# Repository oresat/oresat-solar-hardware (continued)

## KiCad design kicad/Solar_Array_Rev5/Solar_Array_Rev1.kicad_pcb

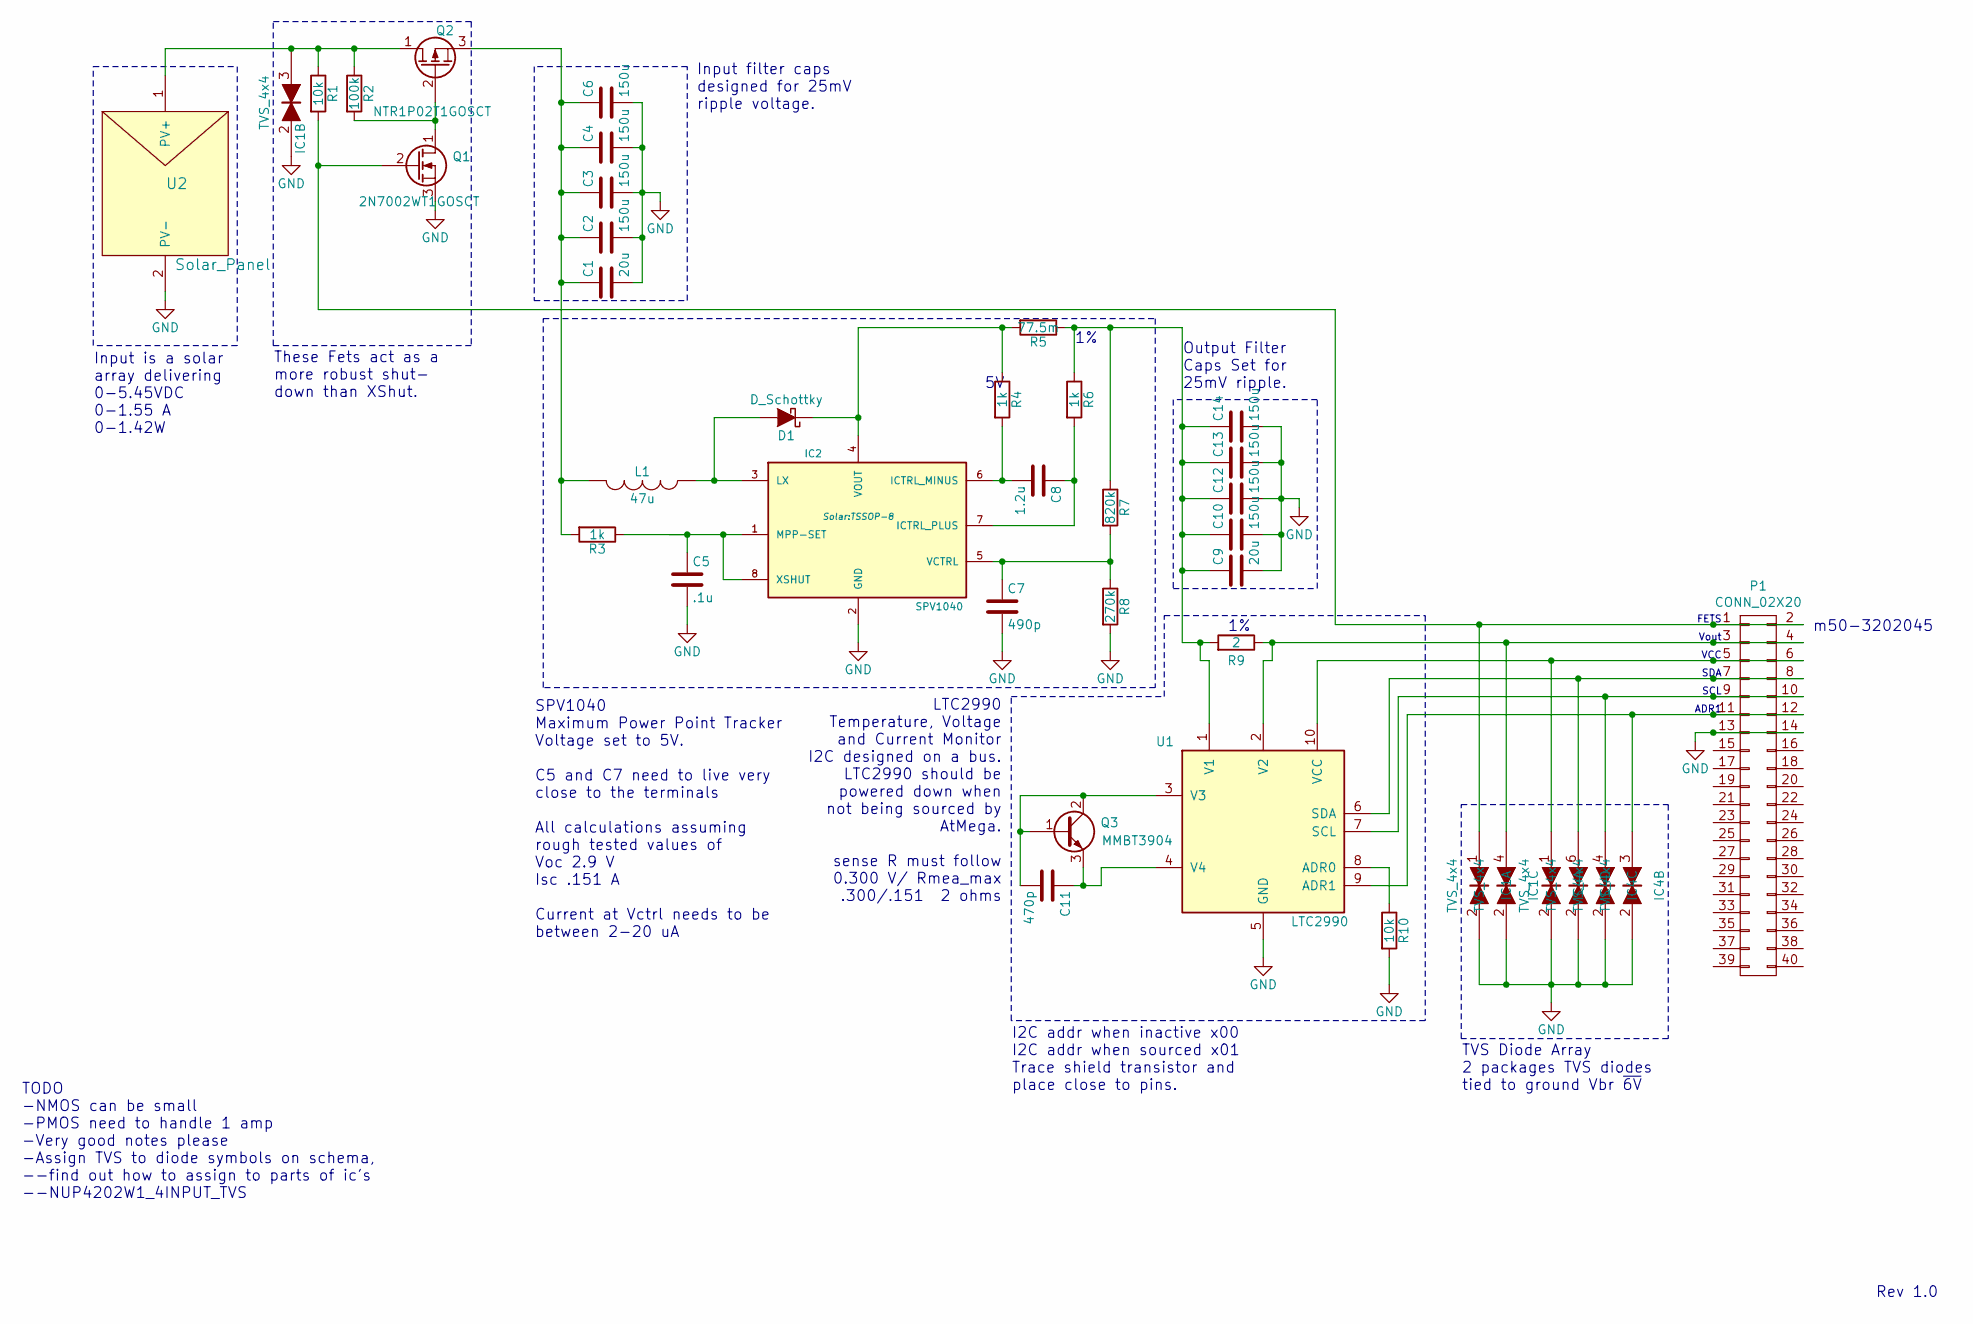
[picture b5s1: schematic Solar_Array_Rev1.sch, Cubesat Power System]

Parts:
C1, C9: 20u; C_0805
C2, C3, C4, C6, C10, C12, C13, C14: 150u; C_1210
C5: .1u; C_0603
C7: 490p; C_0603
C8: 1.2u; C_0805
C11: 470p; C_0805
D1: D_Schottky; SOD-323
IC1, IC4: TVS_4x4; SC-70-6
IC2: SPV1040; TSSOP-8
L1: 47u; Inductor_1212
P1: CONN_02X20; CS0_40PIN_HEADER
Q1: 2N7002WT1GOSCT; SC-70
Q2: NTR1P02T1GOSCT; SOT-23
Q3: MMBT3904; SOT-23
R1, R10: 10k; R_0603
R2: 100k; R_0603
R3, R4, R6: 1k; R_0603
R5: 77.5m; R_0603
R7: 820k; R_0603
R8: 270k; R_0603
R9: 2; R_0603
U1: LTC2990; MSOP-10
U2: Solar_Panel; ALTA_GA_CELL

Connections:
GND: C1.2, C2.2, C3.2, C4.2, C5.2, C6.2, C7.2, C9.2, C10.2, C12.2, C13.2, C14.2, IC1.2, IC2.2 (GND), IC4.2, P1.13, P1.14, Q1.3 (S), R8.2, R10.2, U1.5 (GND), U2.2 (PV-)
unnamed: C1.1, C2.1, C3.1, C4.1, C6.1, L1.2, Q2.3 (S), R3.2
unnamed: C5.1, IC2.1 (MPP-SET), IC2.8 (XSHUT), R3.1
unnamed: C7.1, IC2.5 (VCTRL), R7.2, R8.1
unnamed: C8.1, IC2.7 (ICTRL_PLUS), R6.2
unnamed: C8.2, IC2.6 (ICTRL_MINUS), R4.2
unnamed: C9.1, C10.1, C12.1, C13.1, C14.1, R5.1, R6.1, R7.1, R9.2, U1.1 (V1)
unnamed: C11.1, Q3.3 (E), U1.4 (V4)
unnamed: C11.2, Q3.1 (B), Q3.2 (C), U1.3 (V3)
unnamed: D1.1 (K), IC2.4 (VOUT), R4.1, R5.2
unnamed: D1.2 (A), IC2.3 (LX), L1.1
unnamed: IC1.1, P1.1, P1.2, Q1.2 (G), R1.2
unnamed: IC1.3, Q2.1 (D), R1.1, R2.1, U2.1 (PV+)
unnamed: IC1.4, P1.3, P1.4, R9.1, U1.2 (V2)
unnamed: IC4.1, P1.5, P1.6, U1.10 (VCC)
unnamed: IC4.3, P1.11, P1.12, U1.9 (ADR1)
unnamed: IC4.4, P1.9, P1.10, U1.7 (SCL)
unnamed: IC4.6, P1.7, P1.8, U1.6 (SDA)
unnamed: Q1.1 (D), Q2.2 (G), R2.2
unnamed: R10.1, U1.8 (ADR0)

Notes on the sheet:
Input is a solar array delivering 0-5.45VDC 0-1.55 A 0-1.42W
Vout
VCC
SDA
ADR1
Rev 1.0
SCL
TODO -NMOS can be small -PMOS need to handle 1 amp -Very good notes please -Assign TVS to diode symbols on schema, --find out how to assign to parts of ic's --NUP4202W1_4INPUT_TVS
FETS
These Fets act as a more robust shut- down than XShut.
Input filter caps designed for 25mV ripple voltage.
SPV1040 Maximum Power Point Tracker Voltage set to 5V. C5 and C7 need to live very close to the terminals All calculations assuming rough tested values of Voc 2.9 V Isc .151 A Current at Vctrl needs to be between 2-20 uA
Output Filter Caps Set for 25mV ripple.
LTC2990 Temperature, Voltage and Current Monitor I2C designed on a bus. LTC2990 should be powered down when not being sourced by AtMega. sense R must follow 0.300 V/ Rmea_max .300/.151 ~ 2 ohms
TVS Diode Array 2 packages TVS diodes tied to ground Vbr ~6V
m50-3202045
I2C addr when inactive x00 I2C addr when sourced x01 Trace shield transistor and place close to pins.

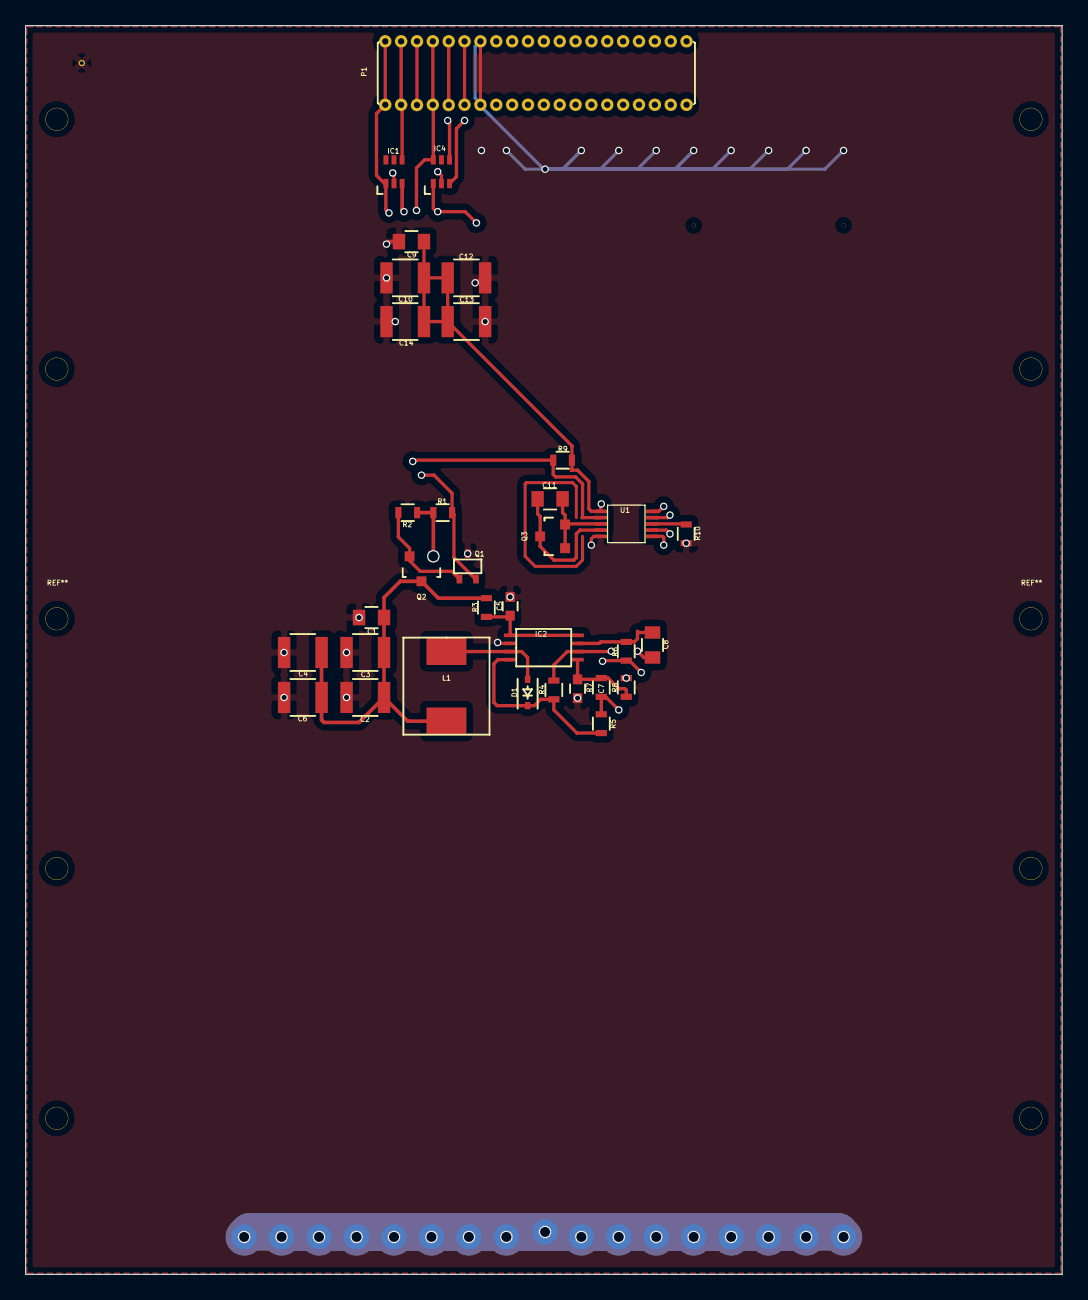
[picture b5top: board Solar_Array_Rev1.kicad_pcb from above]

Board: 4 copper layers, 83.0 x 100.0 mm, 35 parts (1 on the bottom side), 20 nets.

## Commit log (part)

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2016-01-24 Added and addressed 4 LTC2990's.
2016-01-25 Added SPV1040 circuitry.
2016-01-26 Added automatic powercycle, finished current,temp and voltage sense.
2016-01-26 Compoonent values selected for some caps.
2016-01-27 Deleted extraneous files, updated schema symbol for SPV1040 because pretty. Removed other addressed modules. Added button for xshut for testing.
2016-01-28 Removed extraneous circuitry, added more component values, swapped 1x2 conn with 1x3 conn.
2016-02-03 Generated Netlist, blocked all I/O to 1x6 pin array.
2016-02-11 Updated todo, updated TVS diode.
2016-02-13 Finished footprints for SPV1040, LTC2990, TVS Diodes, generated netlist. Initial PCB config finished.
2016-02-19 Fixed missing/broken ground.
2016-03-03 Rebuilt LTC2990 footprint. Regenerated Gerb Files -Changed LTC2990 pad width from .334 to .305 -Replaced old footprint and generated gerb files note that design check passed without warnings.
2016-03-09 Fixed glaring errors in layout. Changed footprints.
    -Fixed LTC2990 and SPV1040 footprints to reflect phsical layout
    -Fixed board layout to accomodate actual design.
2016-03-09 Added ground tacks.
2016-03-30 Created Rev 1 -Added several new filter caps. -Added more accurate inductor values. -Added Current limiting resistor. -Updated all component values to reflect functioning values.
2016-04-06 Added Rev1_BOM, added todo's to schematics
2016-04-09 Added PDF's and generated SVG's. Updated Component values.
    -Fixed mixing capacitor values on board layout.
    -Added 'PDF' folder to docs
    -Generated svg and pdf's of project
2016-04-12 Added components, updated BOM -Added parallel filter cap input. -Updated BOM to reflect new parts.
2016-04-16 Removed D2. Set R9 as NP resistor and tied sensor to R5.
2016-04-24 Finished Layout, updated notes, regenerated PDF's - Finished the board layout with obnoxious stitching. - Updated component notes for IC's - Regenerated F/B copper PDF's and schema PDF's
2016-05-13 Added data sheet for new ZSPM cihp.
2016-05-25 Added MPPT folder and started design for chip.
2016-06-01 Assigned Pin functions to ST microcontroller. -Found CAN TX/RX and assigned. -Found ADC in's for voltage/current sense. -Found TIM1 chn 1/3 for PWM control
2016-06-04 Including backups to push.
2016-06-18 Added Rev 5 and saved files into doc.
2016-06-18 Created and added 40 pin header to Solar lib.
2016-06-18 Faked 3d drawing of pin header.
2016-06-18 PDF of Rev5 placed in PDF folder under doc.
2016-06-24 Added Mechanical drawings/folder. Finished layout. -Added /mechanical to /solar -Added solar stl -Finished layout
2016-06-27 Created new Part library for project
2016-06-27 Deleted lock preventing non-Andrews from accessing sch/brd
2016-07-08 Continued copying designs into eagle.
2016-07-10 Oh another temp file
2016-07-11 Added LTC2990.
2016-07-20 Added pinheader to schematic.
2016-07-22 Added inductor switching reg.
2016-07-22 Updated Schematic and Layout.
2016-07-24 Added inductor for switching reg to schema/board
2016-07-27 Removed lockfiles I'm a bad person for commiting them
2016-07-27 Added todo and started polygons
2016-07-30 Finished preliminary board layout
2016-09-10 Added Block Diag
2016-09-10 Formatted Link
2016-09-10 Added text, links
2016-09-10 Yay markdown!
2016-09-10 Updated Block Diagram
2016-09-26 Created STM32 MCU
2016-09-28 Added 3.3v CAN Transceiver symbol and footprint
2016-09-28 Added symbols and footprints to drawing.
2016-10-05 Nets, Caps, GND oh my.
2016-10-17 Pushing changes from Space Electronics workshop - no more TVS diodes, need onboard regulator, etc.
2016-10-19 Added net annotations
2016-10-19 Connected SWD to STM32
2016-10-27 Board routing and fun times.
2016-10-28 More routing fun times goody.
2016-11-02 Finished board layout, fixed upside-down NPN pinout.
2016-11-05 We deciderated: STM for the win. We're dorks.
2016-11-10 Layout fun. Preliminarily finished.
2016-11-12 Added 1212 footprint for new inductor
2016-11-13 v1 solar array. Minor cleanup on the SPV inductor left, but not critical. Moved to two layers, cleaned up polygons, added stiching vias, tightened up, moved tnames around, and basic OCD cleanup.
2016-11-26 Decided to double check the components calculates and inso fell into a deep rabbit hole. So, so many rabbits. See the google doc, which should become a markdown file soon, which shows the changes in 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
2016-11-26 Up EN divider on SPS.
2016-11-27 LInk to rev 1
2016-12-17 Mild cleanup: better stapling, moved positive PV rail above connector for better ground... aaaaand discovered that the connector is going to hit the aluminum frame. Whoops.
2016-12-31 OK can this be the last mod before we send this off? Please? New tab configuration goes through board slots and then bends around, lots of wins hopefully for strain relief and better current paths. N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
2017-01-23 Changed Alta Cell to be 90.5 mm long; the datasheet is ALWAYS right :)
2017-01-27 Created and format Design docs
2017-01-28 Example format of the parts documentation.
2017-02-05 updated the README file.
2017-02-06 Fixing component errors; Q1 is an SOT-23 not an SC-70, some components were out of stock, had wrong attributes, etc. BOM is now mostly error free.
2017-02-15 Oriented some silk and values for easier stuffing
2017-03-03 1u solar panel breakout board, take one.
2017-04-10 Minor changes to debugging and programming breakout - silkscreen on the bottom, longer neck, approved DRC warnings.
2017-04-15 Removed empty project
2017-04-17 Finished rough draft.
2017-05-20 Changed sensor cap to correct value on schematic. Added missing 10k PB8-BOOT pin.
2017-09-01 First version of the 1.1 solar panel. Keeping 1.0 for future reference.
2017-12-17 Breakout for the TS52002 buck MPPT IC.
2018-01-31 Begin v2 solar panel work. Move to the ZSPM4521 MPPT IC which we hope is on its way despite the EOL, move to the TPS63070x buck-boost converter so we can go from 2 to 12 V for the 3.3V supply, add LT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
2018-02-04 Removed unused parts, and moved common OreSat Card parts to the oresat-eagle-libraries repo.
2018-02-18 Cleaned up a lot of libraries, nailed down ZSPM, LTC, and the first bits of the TPS. Some preliminary layout.
2018-02-22 Added debug LED by side hole for debugging.
2018-02-25 Cleaned up old library files. Moved the useful ones to oresat-eagle-library, removed the rest.
2018-02-25 Fixed some attributes on parts.
2018-02-26 Added part numbers to odd connectors.
2018-10-07 Added latest DXF drawing to board. Added some radii, cleaned up board layers, still need to fix the main solar connector to the TH part.
2019-03-04 Uploading the solar simulator like I should have forever ago
2019-03-13 Outline, ground plane, and DXF cleanup.
2019-03-15 Beeeg cleanup. Converted passives to RCL custom, cleaned up switcher layout, started the Big Stitch, and cleaned up where possible. Left to do: LED footprint cleanup, and routing to dump their heat t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
2019-03-17 Copper cleanup of solar simulator board. Left LEDs about where they were as much as possible, moved origins ot center on LEDs, tried to sink as much heat to the bottom layer as possible.
2019-03-25 Big massive shrinkification and OCDification after discussing board with Catie. Moved the Nano off to the overhang area so we could arbitrarily reduce the distance to the solar cell, added two extra 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
2019-03-26 added BOM and cleaned up schematic a bit
2019-03-26 updated it all to fit new board and fit in vacuum chamber better
2019-03-27 Documentation shenanagins
2019-05-06 updated boost design to include output settings
2019-06-04 lt1618 boost with Iadj ramp up
2019-06-29 Cleanup to the solar repo as we ramp up on the v3 modules.
2019-07-07 updated datasheets to reflect mppt changes and added new chips to eagle
2019-07-12 Updating documentation and progress on next solar rev
2019-07-16 board layout to include new mppt design
2019-07-17 Added datasheet for new temp sensor and solar board updates
2019-07-18 updated BOM
2019-07-19 made the mppt schematic less horrible, more layout tweaks
2019-07-21 fixed screw up on can layout
2019-07-23 Updated symbols. Added decent diode for LT1618. Switched LTC4411 for the LTC4412 due to the 2S change. Added shutdown to LT1618 and TPS ICs, as well as to the LTC4412. LTC4412 has back-to-back MOSFET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
2019-07-25 Fixed I2C lines from STM32, moved 3.3V system to work right off of the solar panel instead of after the MPPT, some routing clean up. Left to do: stitching, polish, and figure out about the damn debug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
2019-07-29 Switched debug port to a FFC (yes we'll regret this but c'est la vie), fixed MAX pin, cleanup, stiching, last minute checks.
2019-07-29 Cleaned up TNAME layer.
2019-07-30 Whoops forgot board file.
2019-07-31 updated FFC debug breakout
2019-08-16 updates solar sim solidworks files
2019-08-20 "auto-generated from update_repos.py"
2019-10-11 added manufacturer informaton for temp sensors on solar sim, tweaks to 1u_panel, added very in progress driver for solar simulator. Documentation inboud
2019-10-12 solar simulator documentation, grammar corrections in solar documentation.
2019-11-15 schematic for solar sim 2.0
2019-12-29 added solar simulator rev 2.0, moved eagle files to oresat eagle repo
2020-01-19 revisions for solar simulator 2.0, removed outdated solarsim.lbr, new parts in oresat-eagle repo
2020-01-24 changed from slots to vias for barrel jack conenctors on solar simulator
2020-01-27 Final cleanup! Moved things around for final cleanup, fixed BOM via oresat-rcl, etc.
2020-06-26 next rev of solar board
2020-06-30 added 0 ohm jumpers to isolate certain blocks, moved debug to vout, grounded boot0, added note about screwhead avoidance, layout tweaks, added indicatr LED on 3.3V line
2020-07-08 Updated cell footprint and tdoc to be more clear.
2020-07-08 Added RBF connector.
2020-07-09 Updated DXF layer based on latest solar panel CAD.
2020-07-23 UUuugggghhhh merged David's changes, NOW everything is nicely cleaned up with his attributes.
2020-09-09 Added capacitor bank circuit for MCU and updated BOM
2020-10-22 tweaks to solar V5.1
2020-10-24 More TPLACE/TNAME cleanup.
2020-12-06 swapped 3.3V sps to the tps63060 because supply chains are hard
2020-12-15 switched Q2 to a dual PFET, which it always should have been
2021-01-12 Finally fixed the LTC4412 solder mask on Pin 2. Finally.
2021-03-22 V5.2, fixed temp sensors AGAIN, and added fiducials
2021-04-18 v5.3 solar boards. Now with fiducials, a more direct cap bank, cleaned up 3.3V SPS area, and minor other little fixes.
2022-05-17 Bring docs - PDFs - up to v5.3
2023-05-02 Upgraded gitignore to include local files and kicad files.
2023-05-03 Switch to PSAS naming convention!
2023-05-28 Update test-plan.md
    Updated charging voltage to the correct value.
2023-05-29 Update test-plan.md
    Updated solar module current draw error range based on data acquired from testing 9 modules.
2023-05-29 Fixed R12 value to make VOUT to 8.4V max. Was at 8.6V max. Also cleaned up some EAGLE import issues, mostly text size and labels.
2024-06-02 possibly ready for silicon panel design review?
2024-08-20 updating remote repo for design review
2024-09-14 Updated all PN/DS/DPN/MPN/etc. for silicon solar module components
2024-09-30 Polish on Jack's final design. Swapped out rectangles for zones on multiple layers, cleaned up a lot of small layout bits, fixed some mechanical crashes with screw heads, fixed up the silk screen, an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
2024-10-20 updated a few parts based on availability
2025-01-21 Removes a lot of old crufty projects, like the original solar simulator, and design files that are horribly out of date, and some weird backup files.
2025-01-29 changes for silicon solar module bringup tasks
2025-05-18 changes for bringup issues on Si Solar module
2025-09-16 Yeah, renamed everything because consistancy.
2025-09-16 Moved solar module breakout board (for the Harwin connector) to KiCad.
2025-09-18 Fixed ERC errors, including unused blocks and some power stuff.
2025-09-20 More routing work, pulled power routing onto another layer
2025-09-21 Fixed most DRC errors
2025-09-22 Silkscreen polish during design review, updated all DRU from imported file.
2025-09-24 Final polishing before fab. Fixed I2C pullups, removed some silly test points, lots of good zone planning on layer 3, cleaned up solar ideal diodes, moved LED to a blink light instead of power light.
2025-10-21 Fixed small issue in MCXN symbol
2026-01-07 Last polish, just stitching
